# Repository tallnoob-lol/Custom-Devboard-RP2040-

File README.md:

# Custom-Devboard-RP2040-
Custom development board using the RP2040 microcontroller with 20 GPIO pins, 4 ADC pins, 2 user-controlled LED, 1 user button, etc.

## Why this?
I started this project, because I wanted to learn more about KiCAD. Also, I wanted a DevBoard that i could easily prototype with. As, most of the DevBoards online had some quirks like random GPIO arrangement or doesnt have any means of displaying a output on the board itself. So, I built this and it really helped in many ways.

## Features
- RP2040 microcontroller at 133MHz
- USB Type-C connector
- max 600mA power draw
- Boot and reset buttons
- Power & 2 User LED
- GPIO header pins
- Debug connector
- Bootsel, Reset & User Buttons

## Hardware Design
The hardware design will include:
- Power by AP2112K-3.3 linear LDO regulator
- 16mB External QSPI flash from W25Q16JVZPIQ TR
- USB-C interface for programming and power
- Clock source: 12MHz Crystal

## Pictures

## Future Improvements
- Add Li-ion compatibility
- On-Board tiny OLED display
- Improved portability for prototyping

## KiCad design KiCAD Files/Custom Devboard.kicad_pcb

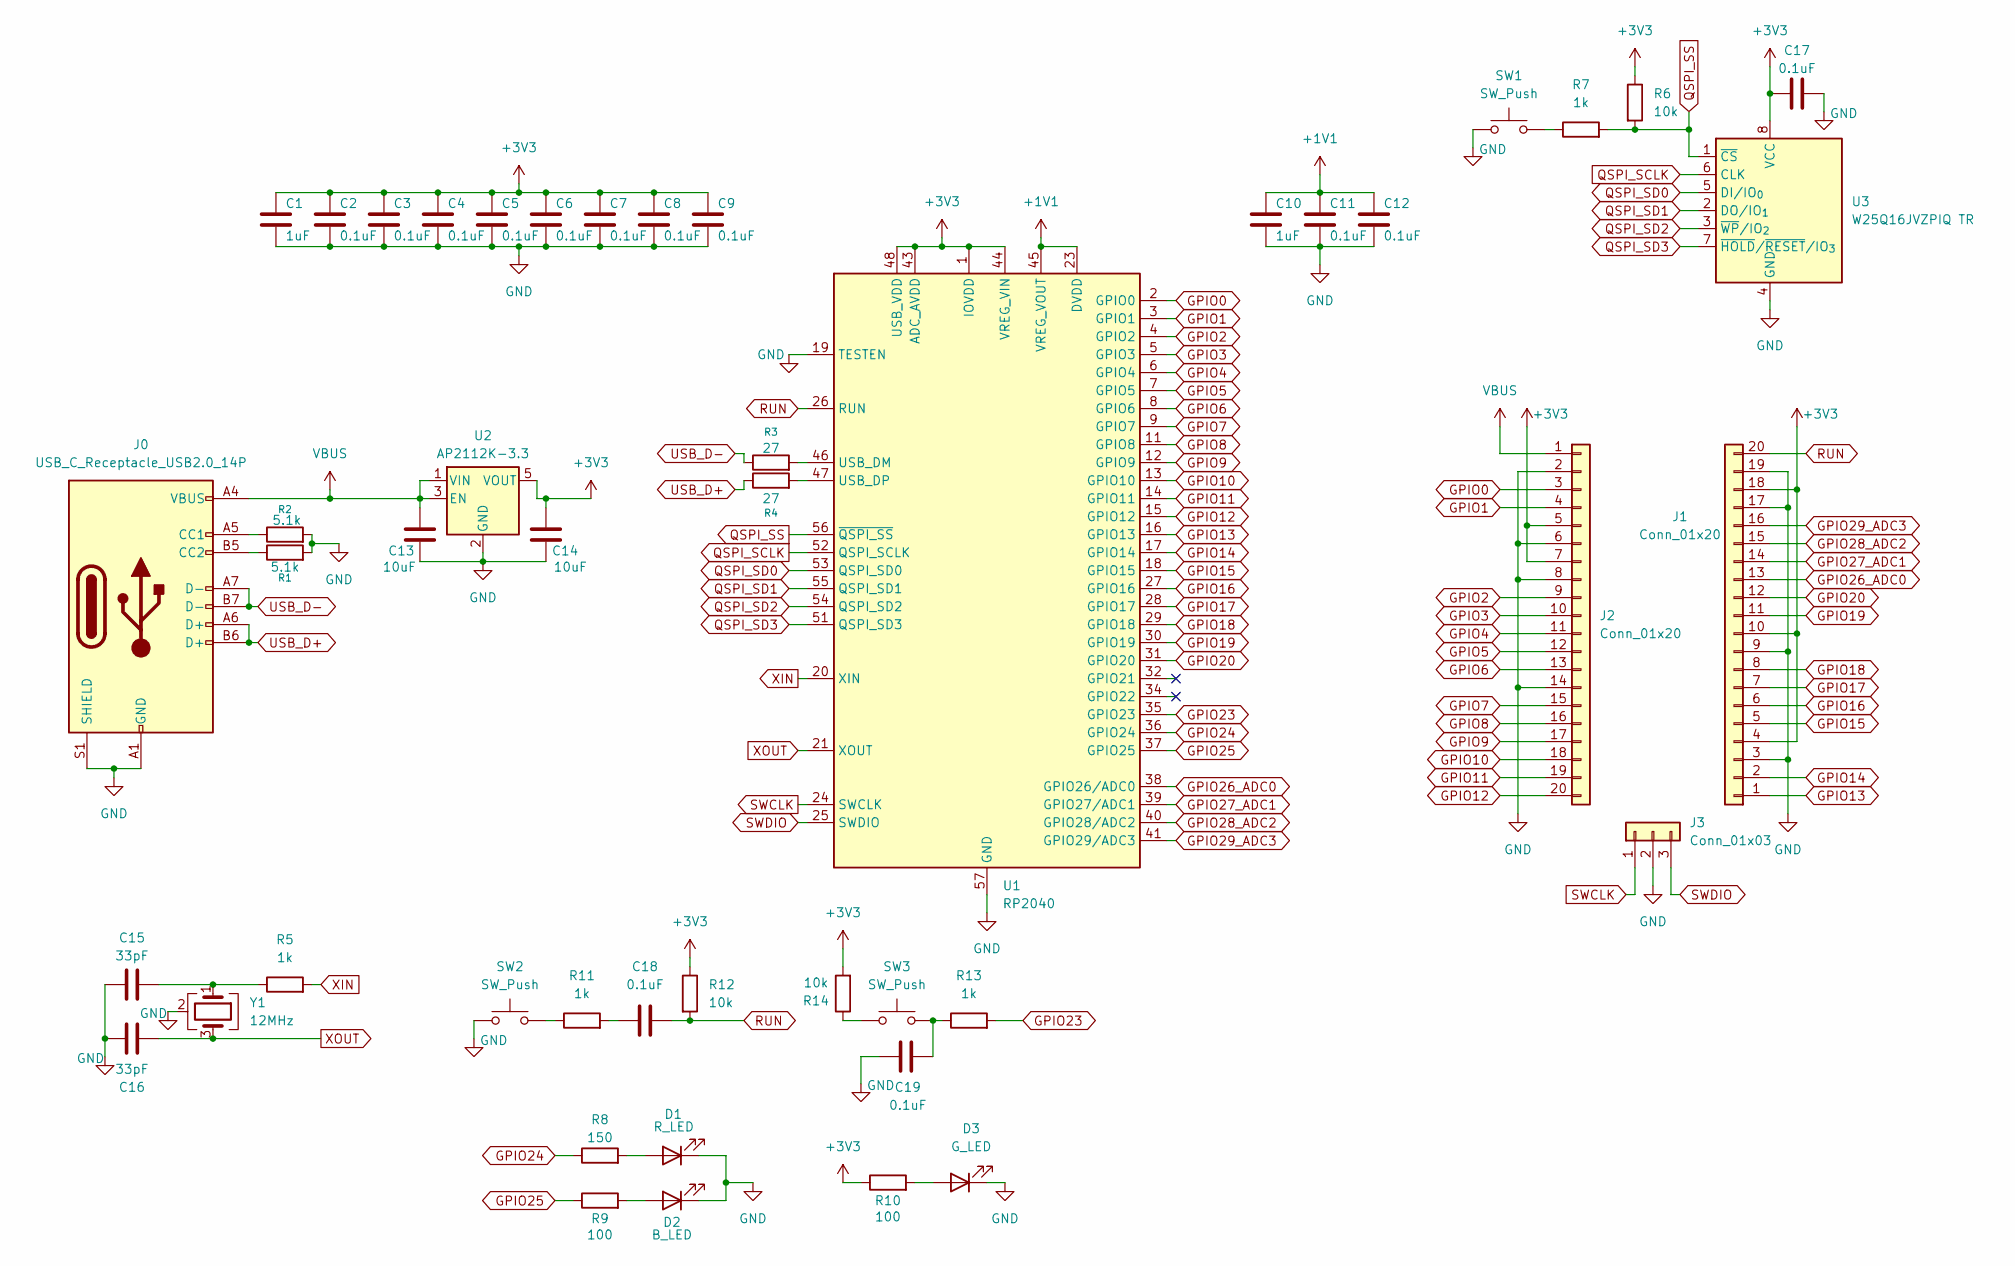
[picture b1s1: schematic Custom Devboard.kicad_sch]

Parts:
C1, C10: 1uF; C_0402_1005Metric
C2, C3, C4, C5, C6, C7, C8, C9, C11, C12, C17, C18, C19: 0.1uF; C_0402_1005Metric
C13, C14: 10uF; C_0603_1608Metric
C15, C16: 33pF; C_0402_1005Metric
D1: R_LED; LED_0603_1608Metric
D2: B_LED; LED_0603_1608Metric
D3: G_LED; LED_0603_1608Metric
J0: USB_C_Receptacle_USB2.0_14P; USB_C_Receptacle_HRO_TYPE-C-31-M-12
J1, J2: Conn_01x20; PinHeader_1x20_P2.54mm_Vertical
J3: Conn_01x03; PinHeader_1x03_P2.54mm_Vertical
R1, R2: 5.1k; R_0402_1005Metric
R3, R4: 27; R_0402_1005Metric
R5, R7, R11, R13: 1k; R_0402_1005Metric
R6, R12, R14: 10k; R_0402_1005Metric
R8: 150; R_0402_1005Metric
R9, R10: 100; R_0402_1005Metric
SW1, SW2, SW3: SW_Push; SW_Push_SPST_NO_Alps_SKRK
U1: RP2040; QFN-56-1EP_7x7mm_P0.4mm_EP3.2x3.2mm
U2: AP2112K-3.3; SOT-23-5
U3: W25Q16JVZPIQ TR; Winbond_USON-8-1EP_3x2mm_P0.5mm_EP0.2x1.6mm
Y1: 12MHz; Crystal_SMD_3225-4Pin_3.2x2.5mm

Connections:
+1V1: C10.1, C11.1, C12.1, U1.23 (DVDD), U1.45 (VREG_VOUT), U1.50 (DVDD)
+3V3: C1.1, C2.1, C3.1, C4.1, C5.1, C6.1, C7.1, C8.1, C9.1, C14.1, C17.1, J1.4, J1.10, J1.18, J2.5, J2.7, R6.1, R10.1, R12.1, R14.2, U1.1 (IOVDD), U1.10 (IOVDD), U1.22 (IOVDD), U1.33 (IOVDD), U1.42 (IOVDD), U1.43 (ADC_AVDD), U1.44 (VREG_VIN), U1.48 (USB_VDD), U1.49 (IOVDD), U2.5 (VOUT), U3.8 (VCC)
GND: C1.2, C2.2, C3.2, C4.2, C5.2, C6.2, C7.2, C8.2, C9.2, C10.2, C11.2, C12.2, C13.2, C14.2, C15.1, C16.1, C17.2, C19.1, D1.1 (K), D2.1 (K), D3.1 (K), J0.A1 (GND), J0.A12 (GND), J0.B1 (GND), J0.B12 (GND), J0.S1 (SHIELD), J1.3, J1.9, J1.17, J1.19, J2.2, J2.6, J2.8, J2.14, J3.2, R1.2, R2.2, SW1.1, SW2.1, U1.19 (TESTEN), U1.57 (GND), U2.2 (GND), U3.4 (GND), Y1.2 (G), Y1.4 (G)
GPIO0: J2.3, U1.2 (GPIO0)
GPIO1: J2.4, U1.3 (GPIO1)
GPIO2: J2.9, U1.4 (GPIO2)
GPIO3: J2.10, U1.5 (GPIO3)
GPIO4: J2.11, U1.6 (GPIO4)
GPIO5: J2.12, U1.7 (GPIO5)
GPIO6: J2.13, U1.8 (GPIO6)
GPIO7: J2.15, U1.9 (GPIO7)
GPIO8: J2.16, U1.11 (GPIO8)
GPIO9: J2.17, U1.12 (GPIO9)
GPIO10: J2.18, U1.13 (GPIO10)
GPIO11: J2.19, U1.14 (GPIO11)
GPIO12: J2.20, U1.15 (GPIO12)
GPIO13: J1.1, U1.16 (GPIO13)
GPIO14: J1.2, U1.17 (GPIO14)
GPIO15: J1.5, U1.18 (GPIO15)
GPIO16: J1.6, U1.27 (GPIO16)
GPIO17: J1.7, U1.28 (GPIO17)
GPIO18: J1.8, U1.29 (GPIO18)
GPIO19: J1.11, U1.30 (GPIO19)
GPIO20: J1.12, U1.31 (GPIO20)
GPIO23: R13.2, U1.35 (GPIO23)
GPIO24: R8.1, U1.36 (GPIO24)
GPIO25: R9.1, U1.37 (GPIO25)
GPIO26_ADC0: J1.13, U1.38 (GPIO26/ADC0)
GPIO27_ADC1: J1.14, U1.39 (GPIO27/ADC1)
GPIO28_ADC2: J1.15, U1.40 (GPIO28/ADC2)
GPIO29_ADC3: J1.16, U1.41 (GPIO29/ADC3)
unnamed: C15.2, R5.1, Y1.1
unnamed: C18.1, R11.2
unnamed: C19.2, R13.1, SW3.2
unnamed: D1.2 (A), R8.2
unnamed: D2.2 (A), R9.2
unnamed: D3.2 (A), R10.2
unnamed: J0.A5 (CC1), R2.1
unnamed: J0.B5 (CC2), R1.1
unnamed: R7.1, SW1.2
unnamed: R11.1, SW2.2
unnamed: R14.1, SW3.1
unnamed: R3.2, U1.46 (USB_DM)
unnamed: R4.2, U1.47 (USB_DP)
QSPI_SCLK: U1.52 (QSPI_SCLK), U3.6 (CLK)
QSPI_SD0: U1.53 (QSPI_SD0), U3.5 (DI/IO_{0})
QSPI_SD1: U1.55 (QSPI_SD1), U3.2 (DO/IO_{1})
QSPI_SD2: U1.54 (QSPI_SD2), U3.3 (~WP/IO_{2})
QSPI_SD3: U1.51 (QSPI_SD3), U3.7 (~HOLD/~RESET/IO_{3})
QSPI_SS: R6.2, R7.2, U1.56 (~QSPI_SS), U3.1 (~CS)
RUN: C18.2, J1.20, R12.2, U1.26 (RUN)
SWCLK: J3.1, U1.24 (SWCLK)
SWDIO: J3.3, U1.25 (SWDIO)
USB_D+: J0.A6 (D+), J0.B6 (D+), R4.1
USB_D-: J0.A7 (D-), J0.B7 (D-), R3.1
VBUS: C13.1, J0.A4 (VBUS), J0.A9 (VBUS), J0.B4 (VBUS), J0.B9 (VBUS), J2.1, U2.1 (VIN), U2.3 (EN)
XIN: R5.2, U1.20 (XIN)
XOUT: C16.2, U1.21 (XOUT), Y1.3

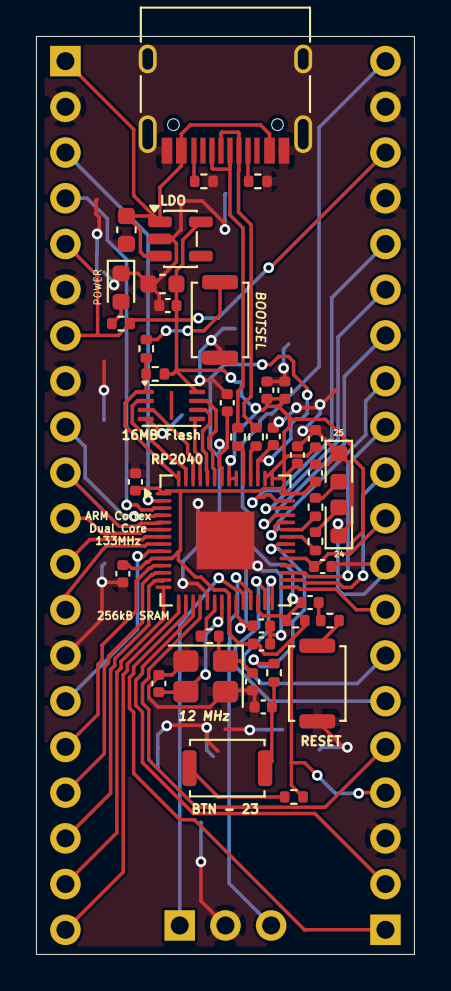
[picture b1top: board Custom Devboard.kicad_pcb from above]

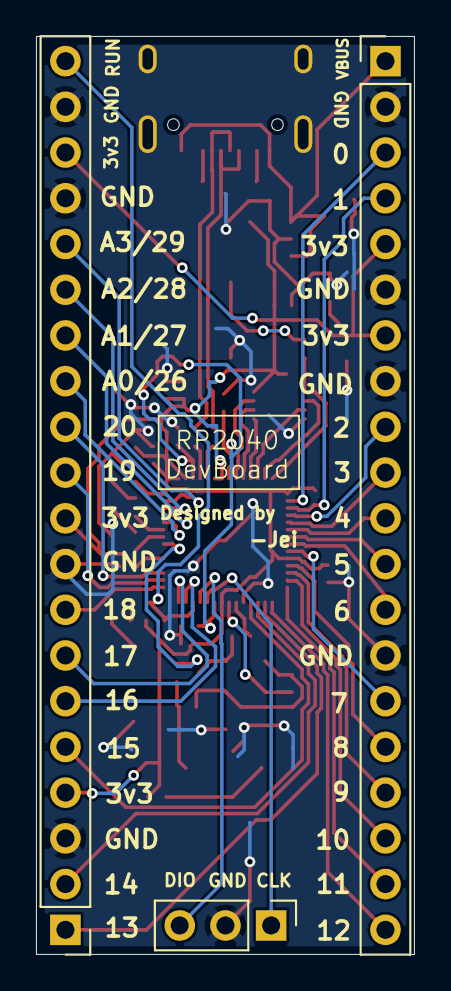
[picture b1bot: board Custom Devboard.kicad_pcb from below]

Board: 2 copper layers, 21.0 x 51.0 mm, 47 parts (3 on the bottom side), 58 nets.

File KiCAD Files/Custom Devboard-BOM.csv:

"Id";"Designator";"Footprint";"Quantity";"Designation";"Supplier and ref";
1;"U3";"Winbond_USON-8-1EP_3x2mm_P0.5mm_EP0.2x1.6mm";1;"W25Q16JVZPIQ TR";;;
2;"R13,R5,R7,R11";"R_0402_1005Metric";4;"1k";;;
3;"C10,C1";"C_0402_1005Metric";2;"1uF";;;
4;"C19,C9,C6,C17,C12,C11,C18,C2,C5,C4,C7,C8,C3";"C_0402_1005Metric";13;"0.1uF";;;
5;"U2";"SOT-23-5";1;"AP2112K-3.3";;;
6;"D1";"LED_0603_1608Metric";1;"R_LED";;;
7;"U1";"QFN-56-1EP_7x7mm_P0.4mm_EP3.2x3.2mm";1;"RP2040";;;
8;"C15,C16";"C_0402_1005Metric";2;"33pF";;;
9;"Y1";"Crystal_SMD_3225-4Pin_3.2x2.5mm";1;"12MHz";;;
10;"R1,R2";"R_0402_1005Metric";2;"5.1k";;;
11;"D3";"LED_0603_1608Metric";1;"G_LED";;;
12;"R4,R3";"R_0402_1005Metric";2;"27";;;
13;"R14,R6,R12";"R_0402_1005Metric";3;"10k";;;
14;"D2";"LED_0603_1608Metric";1;"B_LED";;;
15;"SW3,SW1,SW2";"SW_Push_SPST_NO_Alps_SKRK";3;"SW_Push";;;
16;"C13,C14";"C_0603_1608Metric";2;"10uF";;;
17;"R9,R10";"R_0402_1005Metric";2;"100";;;
18;"R8";"R_0402_1005Metric";1;"150";;;
19;"J0";"USB_C_Receptacle_HRO_TYPE-C-31-M-12";1;"USB_C_Receptacle_USB2.0_14P";;;
20;"J2,J1";"PinHeader_1x20_P2.54mm_Vertical";2;"Conn_01x20";;;
21;"J3";"PinHeader_1x03_P2.54mm_Vertical";1;"Conn_01x03";;;

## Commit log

2026-03-15 Create Pictures
2026-03-15 Rename Screenshot 2026-03-14 170258.png to Pictures/Screenshot 2026-03-14 170258.png
2026-03-15 Rename Screenshot 2026-03-14 170306.png to Pictures/Screenshot 2026-03-14 170306.png
2026-03-15 Rename Screenshot 2026-03-15 162513.png to Pictures/Screenshot 2026-03-15 162513.png
2026-03-15 Rename Screenshot 2026-03-15 162536.png to Pictures/Screenshot 2026-03-15 162536.png
2026-03-15 Rename Screenshot 2026-03-15 162616.png to Pictures/Screenshot 2026-03-15 162616.png
2026-03-15 Rename Screenshot 2026-03-14 170258.png to PCB Front View
2026-03-15 Rename Screenshot 2026-03-14 170306.png to PCB Back View
2026-03-15 Rename Screenshot 2026-03-15 162513.png to PCB Schematics
2026-03-15 Rename Screenshot 2026-03-15 162536.png to PCB Layout - 1
2026-03-15 Rename Screenshot 2026-03-15 162616.png to PCB Layout - 2
2026-03-15 Rename PCB Back View to PCB Back View.png
2026-03-15 Rename PCB Front View to PCB Front View.png
2026-03-15 Rename PCB Layout - 1 to PCB Layout 1.png
2026-03-15 Rename PCB Layout - 2 to PCB Layout 2.png
2026-03-15 Rename PCB Schematics to PCB Schematics.png
2026-03-15 Rename PCB Schematics.png to PCB_Schematics.png
2026-03-15 Rename PCB Back View.png to PCB_Back_View.png
2026-03-15 Rename PCB Front View.png to PCB_Front_View.png
2026-03-15 Rename PCB Layout 1.png to PCB_Layout_1.png
2026-03-15 Rename PCB Layout 2.png to PCB_Layout_2.png
2026-03-15 Rename Custom Devboard-all-pos.csv to KiCAD Files/Custom Devboard-all-pos.csv
2026-03-15 Rename Custom Devboard.csv to KiCAD Files/Custom Devboard-BOM.csv
